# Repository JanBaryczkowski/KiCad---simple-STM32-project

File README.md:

Project based on course made by Philip Salomony
Overview

A hands-on PCB design project using KiCad V6 to create a fully custom STM32-based development board, transitioning from Arduino-style prototyping to professional-grade hardware. The board integrates critical STM32 peripherals (USB, SWD, GPIOs) and follows industry best practices for schematic design, layout, and manufacturing.
Key Features

  Microcontroller: STM32F103C8T6 

    Power Supply:

        5V USB input → 3.3V LDO regulator (e.g., LD1117).

        Decoupling capacitors for noise reduction.

    Connectivity:

        USB 2.0 Full Speed (for programming/debugging).

        SWD Interface (ST-Link compatible).

        GPIO headers (breakout for sensors/actuators).

    Clock: 8MHz crystal + optional 32.768kHz RTC crystal.

    PCB Design:

        2-layer board (optimized for cost).

        Custom silkscreen (logo, pin labels).

        Mounting holes for mechanical stability.

Design Workflow (Following Course Modules)

    Schematic (KiCad V6):

        STM32 symbol creation + pinout planning (STM32CubeIDE).

        Critical circuitry: USB pull-up resistors, boot mode selection, reset circuit.

        ERC (Electrical Rules Check) and footprint assignment.

    PCB Layout:

        Component placement: Prioritize MCU, decoupling caps, and crystal.

        Route high-speed traces (USB, clock) first, followed by power planes.

        Ground pours and via stitching for EMI reduction.

    Routing & Validation:

        Signal integrity: Avoid 90° traces, minimize loops.

        Design Rule Check (DRC) against manufacturer specs (e.g., JLCPCB).

    Manufacturing Prep:

        Generate Gerber files, drill files, and BOM.

        Optional: Order assembled PCBs using KiCad’s fabrication outputs.

Software Tools

    KiCad V6 (Schematic + PCB).

    STM32CubeIDE (Pinout configuration, firmware development).

Learning Outcomes

    Transition from Arduino to custom STM32 hardware.

    Master KiCad workflow (schematic → manufacturing).

    Apply PCB best practices: decoupling, grounding, signal routing.

    Understand STM32 hardware requirements (clocking, USB, SWD).

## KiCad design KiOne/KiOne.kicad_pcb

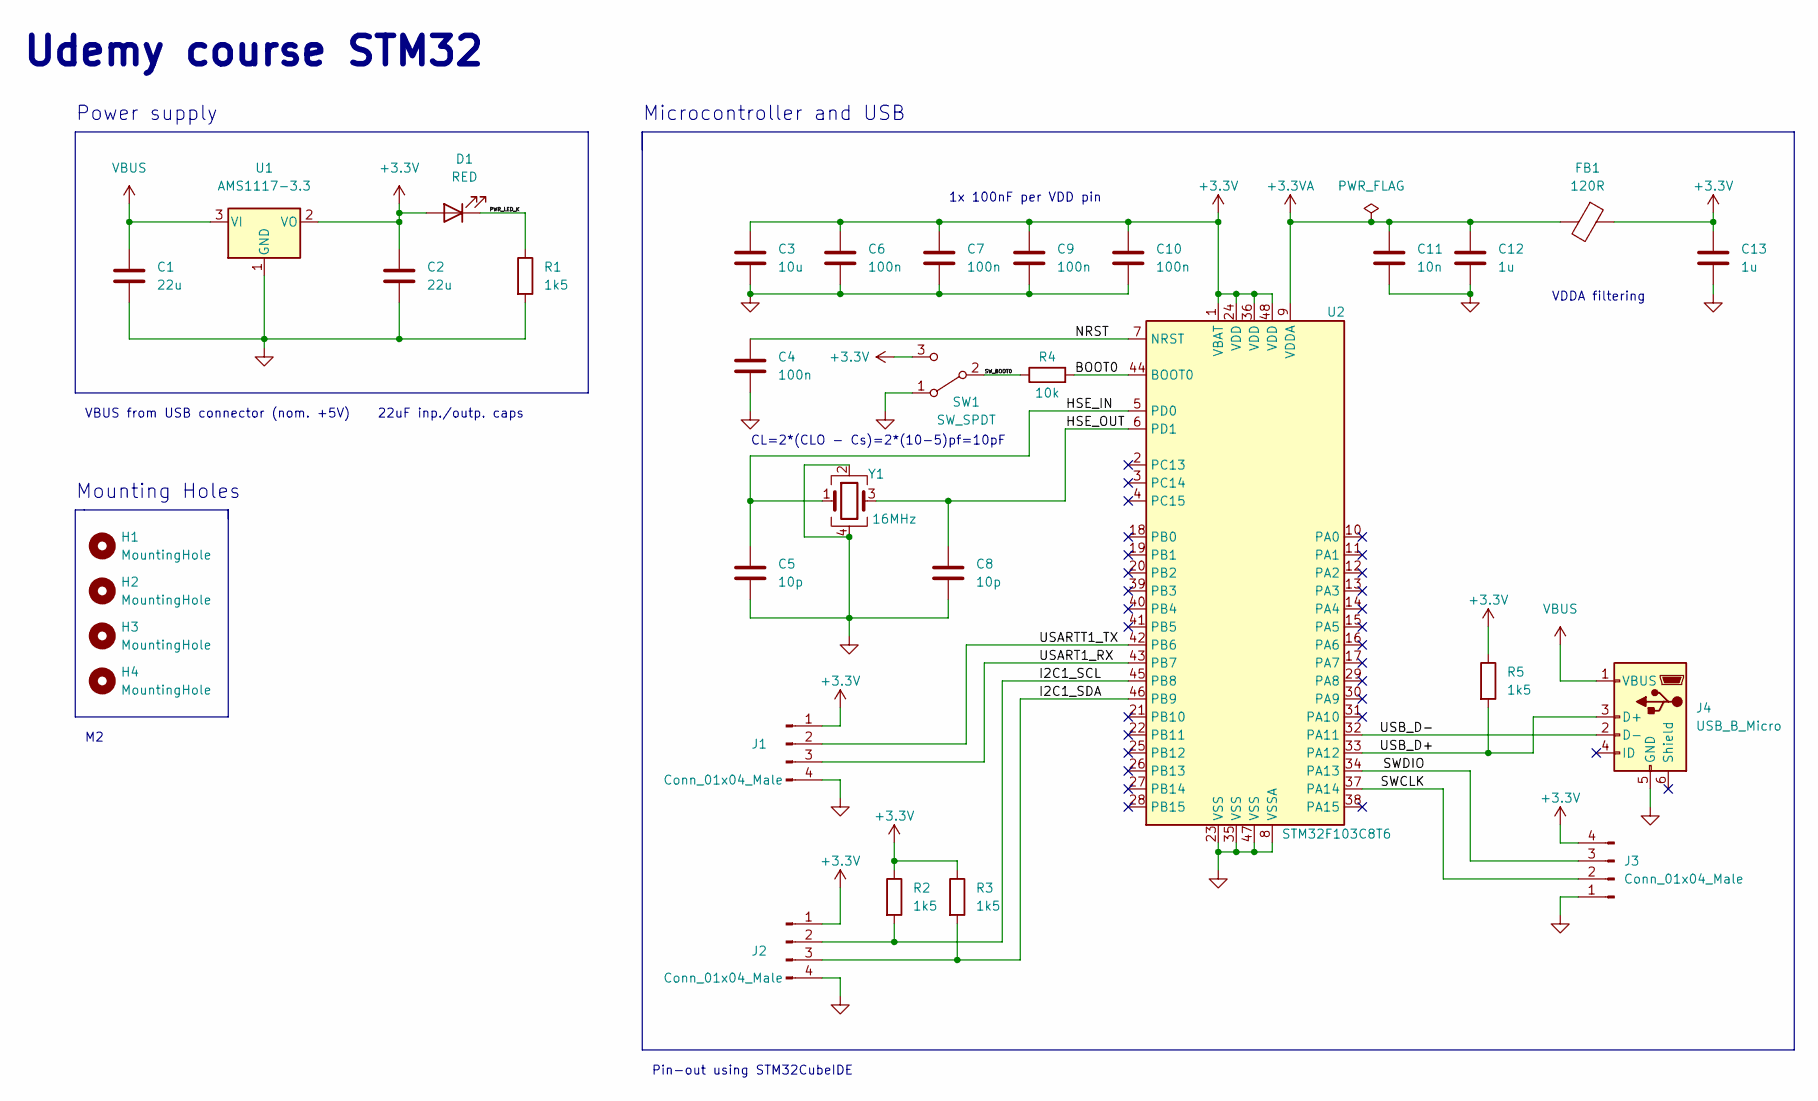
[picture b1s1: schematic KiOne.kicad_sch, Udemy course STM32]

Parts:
C1, C2: 22u; C_0805_2012Metric
C3: 10u; C_0603_1608Metric
C4, C6, C7, C9, C10: 100n; C_0402_1005Metric
C5, C8: 10p; C_0402_1005Metric
C11: 10n; C_0402_1005Metric
C12, C13: 1u; C_0402_1005Metric
D1: RED; LED_0603_1608Metric
FB1: 120R; L_0603_1608Metric
H1, H2, H3, H4: MountingHole; MountingHole_2.2mm_M2
J1, J2, J3: Conn_01x04_Male; PinHeader_1x04_P2.54mm_Vertical
J4: USB_B_Micro; USB_Micro-B_Wuerth_629105150521
R1, R2, R3, R5: 1k5; R_0402_1005Metric
R4: 10k; R_0402_1005Metric
SW1: SW_SPDT; SW_SPDT_PCM12
U1: AMS1117-3.3; SOT-223-3_TabPin2
U2: STM32F103C8T6; LQFP-48_7x7mm_P0.5mm
Y1: 16MHz; Crystal_SMD_3225-4Pin_3.2x2.5mm

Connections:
+3.3VA: C11.1, C12.1, FB1.2, U2.9 (VDDA)
+3V3: C2.1, C3.1, C6.1, C7.1, C9.1, C10.1, C13.1, D1.2 (A), FB1.1, J1.1, J2.1, J3.4, R2.1, R3.1, R5.1, SW1.3 (C), U1.2 (VO), U2.1 (VBAT), U2.24 (VDD), U2.36 (VDD), U2.48 (VDD)
/BOOT0: R4.2, U2.44 (BOOT0)
/HSE_IN: C5.1, U2.5 (PD0), Y1.1
/HSE_OUT: C8.1, U2.6 (PD1), Y1.3
/I2C1_SCL: J2.2, R2.2, U2.45 (PB8)
/I2C1_SDA: J2.3, R3.2, U2.46 (PB9)
/NRST: C4.1, U2.7 (NRST)
/PWR_LED_K: D1.1 (K), R1.1
/SWCLK: J3.2, U2.37 (PA14)
/SWDIO: J3.3, U2.34 (PA13)
/SW_BOOT0: R4.1, SW1.2 (B)
/USART1_RX: J1.3, U2.43 (PB7)
/USARTT1_TX: J1.2, U2.42 (PB6)
/USB_D+: J4.3 (D+), R5.2, U2.33 (PA12)
/USB_D-: J4.2 (D-), U2.32 (PA11)
GND: C1.2, C2.2, C3.2, C4.2, C5.2, C6.2, C7.2, C8.2, C9.2, C10.2, C11.2, C12.2, C13.2, J1.4, J2.4, J3.1, J4.5 (GND), R1.2, SW1.1 (A), U1.1 (GND), U2.8 (VSSA), U2.23 (VSS), U2.35 (VSS), U2.47 (VSS), Y1.2, Y1.4
VBUS: C1.1, J4.1 (VBUS), U1.3 (VI)

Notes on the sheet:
Pin-out using STM32CubeIDE
VBUS from USB connector (nom. +5V) 22uF inp./outp. caps
1x 100nF per VDD pin
Power supply
Microcontroller and USB
Mounting Holes
VDDA filtering
CL=2*(CLO - Cs)=2*(10-5)pf=10pF
Udemy course STM32

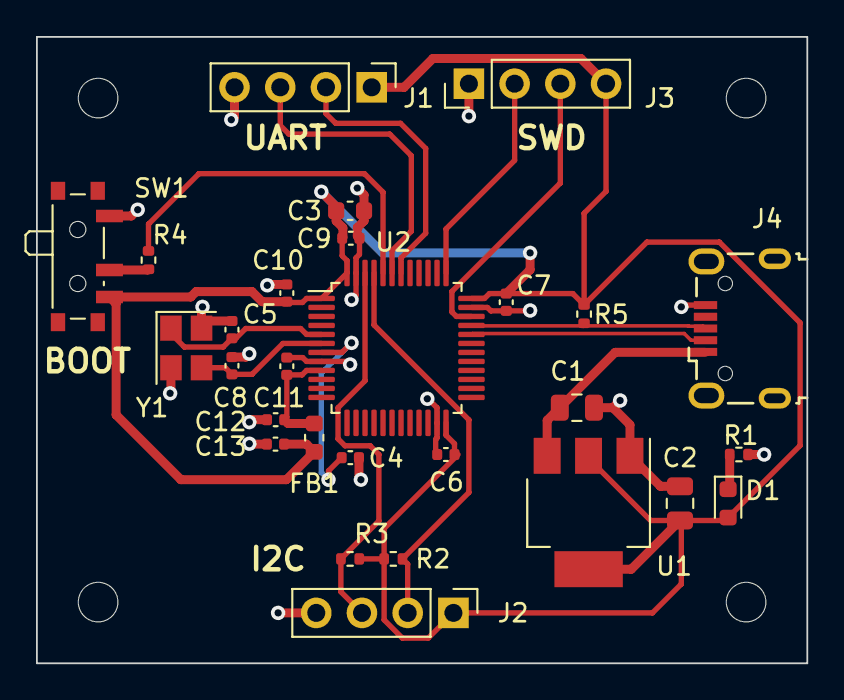
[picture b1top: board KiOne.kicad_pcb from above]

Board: 2 copper layers, 42.8 x 34.8 mm, 32 parts (0 on the bottom side), 18 nets.
